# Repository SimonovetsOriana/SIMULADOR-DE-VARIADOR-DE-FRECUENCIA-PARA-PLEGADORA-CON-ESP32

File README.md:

# SIMULADOR-DE-VARIADOR-DE-FRECUENCIA-PARA-PLEGADORA-CON-ESP32
El simulador de variador de frecuencia para plegadora con ESP32  es una central de mando basada en el microcontrolador de propósitos generales ESP32 y una pantalla de visualización  para simular las funciones de un accionamiento eléctrico que controla la velocidad de un motor trifásico en una máquina plegadora.

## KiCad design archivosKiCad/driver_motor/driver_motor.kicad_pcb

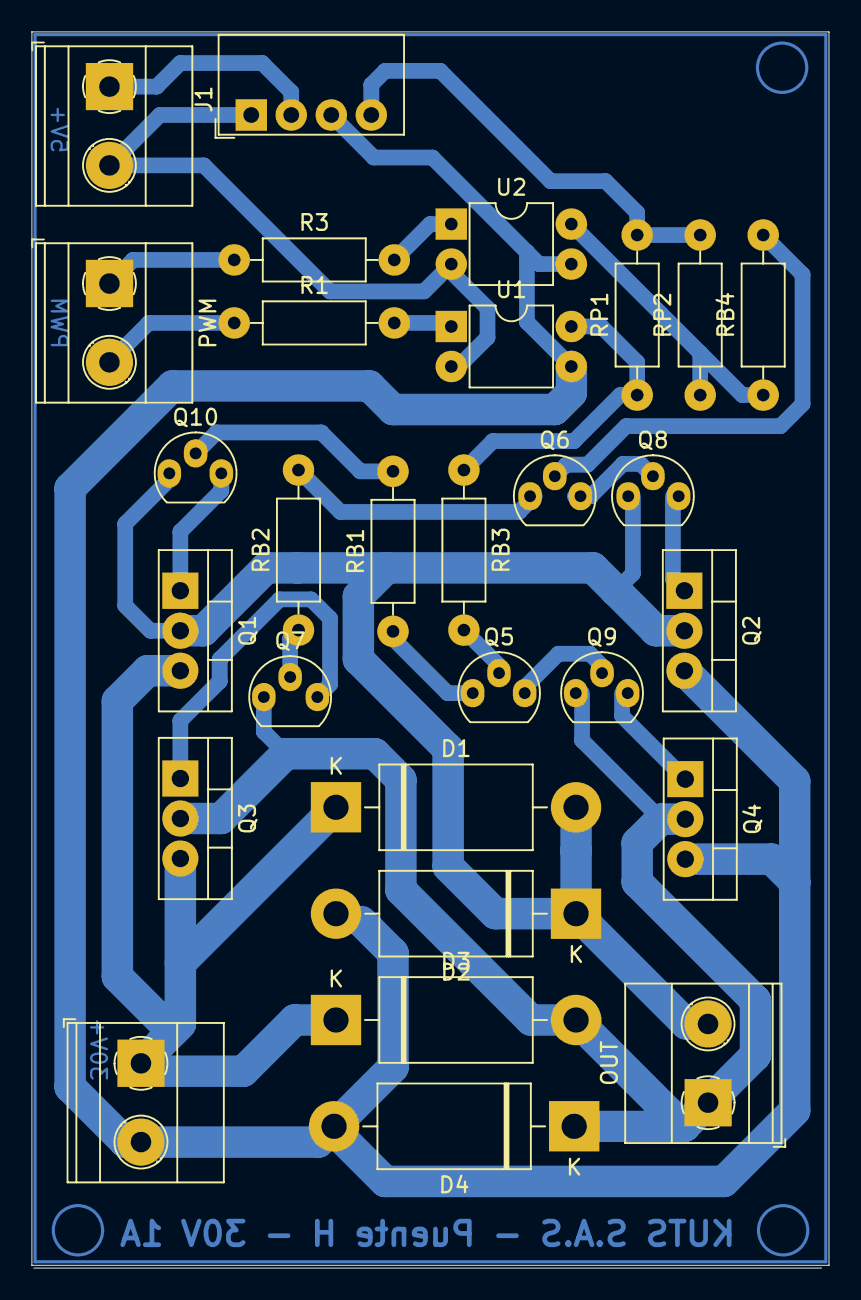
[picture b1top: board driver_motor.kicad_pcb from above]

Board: 2 copper layers, 50.6 x 78.5 mm, 29 parts (0 on the bottom side), 25 nets.

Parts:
5V+, 30V+: Conn_01x02; TerminalBlock_Phoenix_MKDS-1,5-2_1x02_P5.00mm_Horizontal
D1, D2, D3, D4: 1N5401; D_DO-201AD_P15.24mm_Horizontal
J1: Conn_01x04; Converter_DCDC_Murata_CRE1xxxxxx3C_THT
OUT: Conn_01x02; TerminalBlock_Phoenix_MKDS-1,5-2_1x02_P5.00mm_Horizontal
PWM: Conn_01x02; TerminalBlock_Phoenix_MKDS-1,5-2_1x02_P5.00mm_Horizontal
Q1, Q3: TIP42; TO-220-3_Vertical
Q2, Q4: TIP41; TO-220-3_Vertical
Q5, Q6, Q8, Q9: BC337; TO-92
Q7, Q10: BC327; TO-92
R1, R3: 150; R_Axial_DIN0207_L6.3mm_D2.5mm_P10.16mm_Horizontal
RB1, RB2: 28k; R_Axial_DIN0207_L6.3mm_D2.5mm_P10.16mm_Horizontal
RB3, RB4: 120k; R_Axial_DIN0207_L6.3mm_D2.5mm_P10.16mm_Horizontal
RP1, RP2: 10k; R_Axial_DIN0207_L6.3mm_D2.5mm_P10.16mm_Horizontal
U1, U2: PC817; DIP-4_W7.62mm

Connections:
5V: 5V+.1, J1.2
5VI: J1.4, RP1.2, RP2.2
30V: 30V+.1, D1.1 (K), D3.1 (K), Q1.3 (E), Q3.3 (E)
GND1: 5V+.2, J1.1, U1.2, U2.2
GND2: 30V+.2, D2.2 (A), D4.2 (A), J1.3, Q2.3 (E), Q4.3 (E), U1.3, U2.3
unnamed: D1.2 (A), D2.1 (K), OUT.2, Q1.2 (C), Q2.2 (C), Q8.1 (C), Q10.1 (C)
unnamed: D3.2 (A), D4.1 (K), OUT.1, Q3.2 (C), Q4.2 (C), Q7.1 (C), Q9.1 (C)
unnamed: PWM.1, R3.1
unnamed: PWM.2, R1.1
unnamed: Q1.1 (B), Q10.3 (E)
unnamed: Q2.1 (B), Q8.3 (E)
unnamed: Q3.1 (B), Q7.3 (E)
unnamed: Q4.1 (B), Q9.3 (E)
unnamed: Q5.2 (B), RB3.2
unnamed: Q5.1 (C), RB1.1
unnamed: Q5.3 (E), Q9.2 (B)
unnamed: Q6.2 (B), RB4.2
unnamed: Q6.1 (C), RB2.2
unnamed: Q6.3 (E), Q8.2 (B)
unnamed: Q7.2 (B), RB2.1
unnamed: Q10.2 (B), RB1.2
unnamed: R1.2, U1.1
unnamed: R3.2, U2.1
unnamed: RB3.1, RP1.1, U1.4
unnamed: RB4.1, RP2.1, U2.4

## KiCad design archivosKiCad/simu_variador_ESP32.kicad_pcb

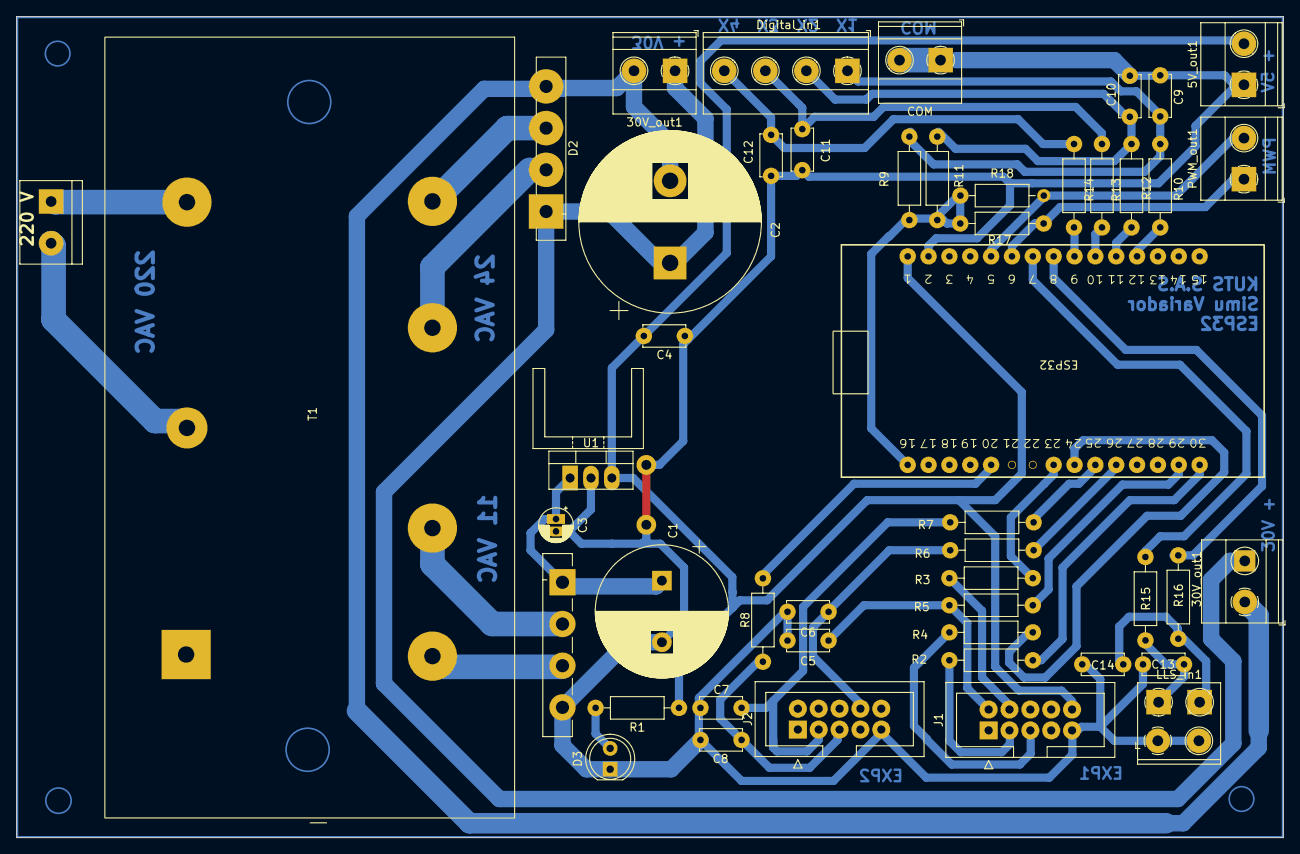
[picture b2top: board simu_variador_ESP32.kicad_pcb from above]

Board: 2 copper layers, 154.3 x 100.0 mm, 48 parts (0 on the bottom side), 41 nets.

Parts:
5V_out1, 30V_out1, 30V_out1#2: Conn_01x02; TerminalBlock_Phoenix_MKDS-1,5-2_1x02_P5.00mm_Horizontal
220V: TerminalBlock_bornier-2_P5.08mm
C1: 4700u; CP_Radial_D16.0mm_P7.50mm
C2: 4700u; CP_Radial_D22.0mm_P10.00mm_SnapIn
C3: 10u; CP_Radial_D4.0mm_P1.50mm
C4: 100n; C_Disc_D5.0mm_W2.5mm_P5.00mm
C5, C6, C7, C8, C9, C10, C11, C12, C13, C14: 474n; C_Disc_D5.0mm_W2.5mm_P5.00mm
COM: Conn_01x02; TerminalBlock_Phoenix_MKDS-1,5-2_1x02_P5.00mm_Horizontal
D1, D2: RS607; Diode_Bridge_Vishay_GBU
D3: LED; LED_D5.0mm
Digital_in1: Conn_01x04; TerminalBlock_Phoenix_MKDS-1,5-4_1x04_P5.00mm_Horizontal
ESP32: ESP32_30pin
J1: EXP1; IDC-Header_2x05_P2.54mm_Vertical
J2: EXP2; IDC-Header_2x05_P2.54mm_Vertical
LLS_in1: Conn_01x02; TerminalBlock_Phoenix_MKDS-1,5-2_1x02_P5.00mm_Horizontal
PWM_out1: Conn_01x02; TerminalBlock_Phoenix_MKDS-1,5-2_1x02_P5.00mm_Horizontal
R1: 280; R_Axial_DIN0207_L6.3mm_D2.5mm_P10.16mm_Horizontal
R2, R3, R4: 100; R_Axial_DIN0207_L6.3mm_D2.5mm_P10.16mm_Horizontal
R5, R6, R7, R8, R10, R12, R13, R14, R15, R16: 390; R_Axial_DIN0207_L6.3mm_D2.5mm_P10.16mm_Horizontal
R9, R11, R17, R18: 10k; R_Axial_DIN0207_L6.3mm_D2.5mm_P10.16mm_Horizontal
T1: Transformer_Myrra_EI30-5_44000_Horizontal
U1: L7805; TO-220-3_Vertical

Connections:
0V: 5V_out1.1, C1.2, C3.2, C4.2, C5.2, C6.2, C7.2, C8.2, C9.2, C10.2, C11.2, C12.2, C13.2, C14.2, COM.1, COM.2, D1.4 (-), D3.1 (K), ESP32.2 (GND), J1.9, J2.9, LLS_in1.3 (Pin_1), U1.2 (GND)
0V_POT: 30V_out1.2, 30V_out1#2.2, C2.2, D2.4 (-)
3,3V: ESP32.16 (3.3v), R9.2, R11.2, R17.2, R18.2
5V: 5V_out1.2, C4.1, ESP32.1 (VIN), J1.10, R1.1, U1.3 (OUT)
11VAC: D1.2, T1.5
24VAC: D2.3, T1.7
30V: 30V_out1.1, 30V_out1#2.1, C2.1, D2.1 (+)
ENC_A: C7.1, J2.3, R7.1
ENC_A_ESP: ESP32.25 (GPIO19), R7.2
ENC_B: C8.1, J2.5, R8.1
ENC_B_ESP: ESP32.20 (GPIO4), R8.2
ESP_CLK: ESP32.24 (GPIO18), R4.2
ESP_CS: ESP32.23 (GPIO5), R3.2
ESP_MOSI: ESP32.30 (GPIO23), R2.2
LCD_CLK: J1.5, R4.1
LCD_CS: J1.4, R3.1
LCD_MOSI: J1.3, R2.1
LLS1: C13.1, LLS_in1.1, R15.1
LLS1_ESP: ESP32.7 (GPIO26), R15.2
LLS2: C14.1, LLS_in1.2, R16.1
LLS2_ESP: ESP32.8 (GPIO25), R16.2
unnamed: C1.1, C3.1, D1.1 (+), U1.1 (IN)
unnamed: D3.2 (A), R1.2
unnamed: D1.3, T1.4
unnamed: D2.2, T1.6
P1_ESP: ESP32.29 (GPIO22), R5.2
P1_EXP1: C5.1, J1.2, R5.1
P2_ESP: ESP32.26 (GPIO21), R6.2
P2_EXP2: C6.1, J2.8, R6.1
PWM1: ESP32.6 (GPIO27), PWM_out1.1, R17.1
PWM2: ESP32.5 (GPIO14), PWM_out1.2, R18.1
VinAC+: 220V.1, T1.2
VinAC-: 220V.2, T1.3
X1: C9.1, Digital_in1.1, R9.1, R10.1
X1_ESP: ESP32.12 (GPIO34), R10.2
X2: C10.1, Digital_in1.2, R11.1, R12.1
X2_ESP: ESP32.11 (GPIO35), R12.2
X3: C11.1, Digital_in1.3, R13.1
X3_ESP: ESP32.10 (GPIO32), R13.2
X4: C12.1, Digital_in1.4, R14.1
X4_ESP: ESP32.9 (GPIO33), R14.2

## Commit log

2025-09-04 Subiendo proyecto finalizado
2025-09-04 Modificacion
